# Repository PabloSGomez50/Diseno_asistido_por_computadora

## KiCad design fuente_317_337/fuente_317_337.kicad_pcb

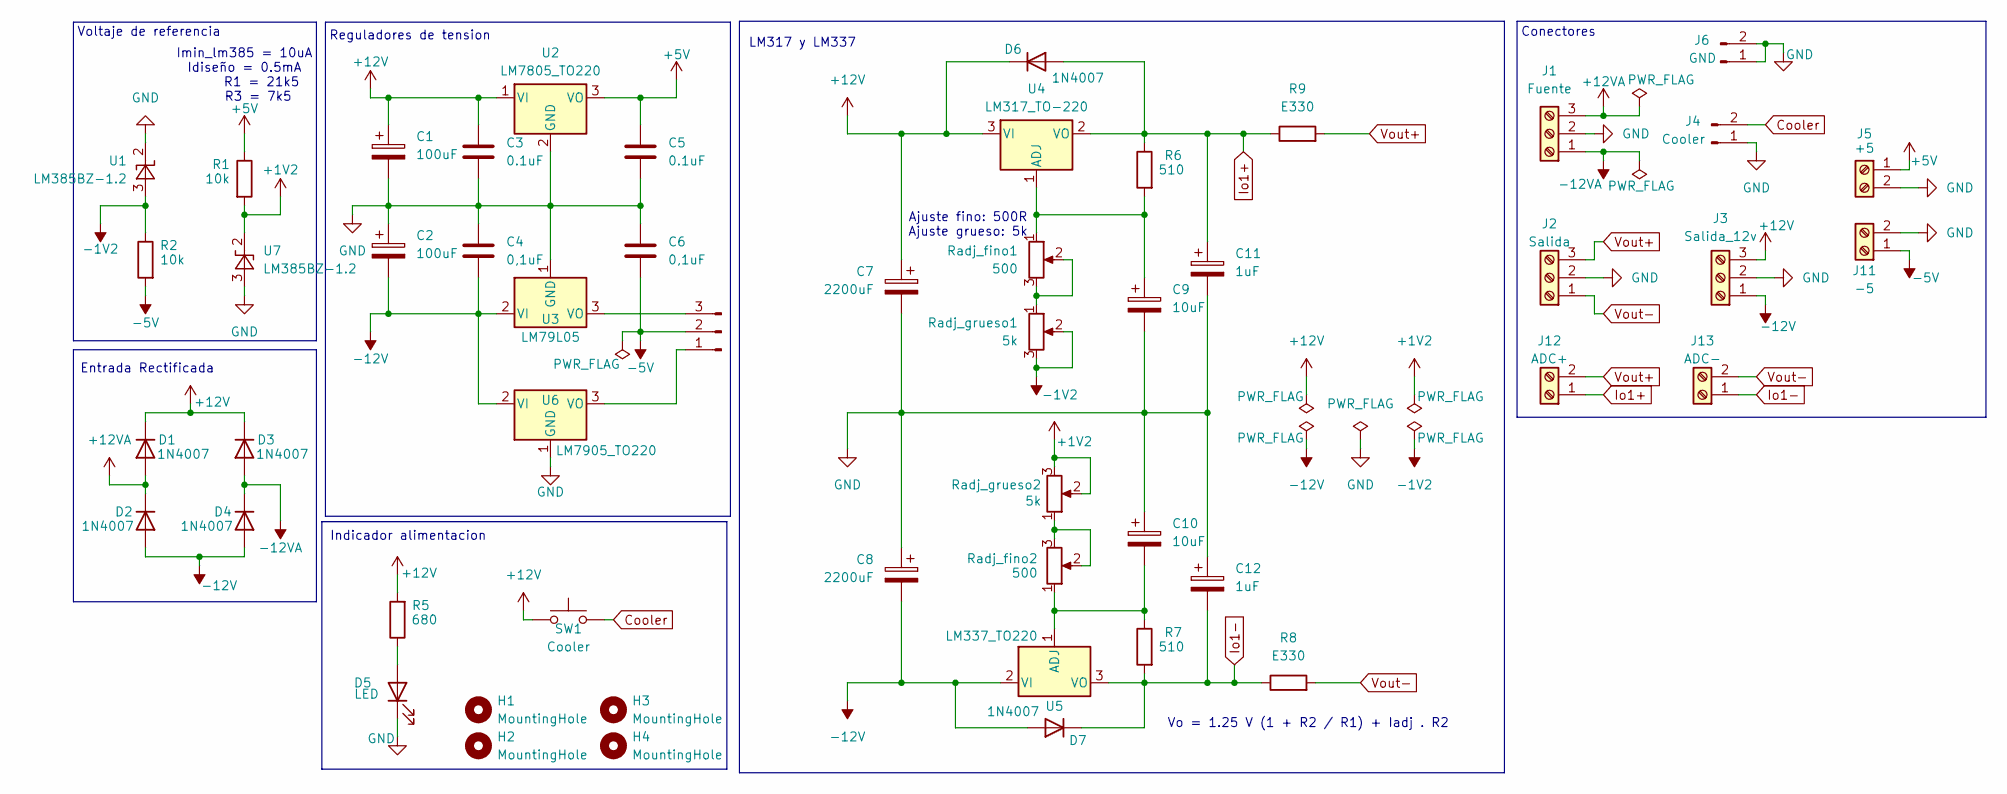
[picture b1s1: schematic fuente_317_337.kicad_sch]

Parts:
C1, C2: 100uF; CP_Radial_D5.0mm_P2.50mm
C3, C5: 0.1uF; C_Disc_D3.0mm_W2.0mm_P2.50mm
C4, C6: 0,1uF; C_Disc_D3.0mm_W2.0mm_P2.50mm
C7, C8: 2200uF; CP_Radial_D16.0mm_P7.50mm
C9, C10: 10uF; CP_Radial_D5.0mm_P2.50mm
C11, C12: 1uF; CP_Radial_D5.0mm_P2.50mm
D1, D2, D3, D4, D6, D7: 1N4007; D_DO-41_SOD81_P10.16mm_Horizontal
D5: LED; LED_D5.0mm
H1, H2, H3, H4: MountingHole; MountingHole_3.2mm_M3
J1: Fuente; TerminalBlock_Phoenix_MKDS-1,5-3-5.08_1x03_P5.08mm_Horizont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
J2: Salida; TerminalBlock_Phoenix_MKDS-1,5-3-5.08_1x03_P5.08mm_Horizont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
J3: Salida_12v; TerminalBlock_Phoenix_MKDS-1,5-3-5.08_1x03_P5.08mm_Horizont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
J4: Cooler; PinHeader_1x02_P2.54mm_Vertical
J5: +5; TerminalBlock_Phoenix_MKDS-1,5-2-5.08_1x02_P5.08mm_Horizont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
J6: GND; PinHeader_1x02_P2.54mm_Vertical
J10: SEL_7905; PinHeader_1x03_P2.54mm_Vertical
J11: -5; TerminalBlock_Phoenix_MKDS-1,5-2-5.08_1x02_P5.08mm_Horizont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
J12: ADC+; TerminalBlock_Phoenix_MKDS-1,5-2-5.08_1x02_P5.08mm_Horizont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
J13: ADC-; TerminalBlock_Phoenix_MKDS-1,5-2-5.08_1x02_P5.08mm_Horizont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
R1: 10k; R_Axial_DIN0207_L6.3mm_D2.5mm_P10.16mm_Horizontal
R2: 10k; R_Axial_DIN0207_L6.3mm_D2.5mm_P5.08mm_Vertical
R5: 680; R_Axial_DIN0207_L6.3mm_D2.5mm_P10.16mm_Horizontal
R6: 510; R_Axial_DIN0207_L6.3mm_D2.5mm_P2.54mm_Vertical
R7: 510; R_Axial_DIN0207_L6.3mm_D2.5mm_P10.16mm_Horizontal
R8, R9: E330; R_Axial_Power_L25.0mm_W6.4mm_P30.48mm
Radj_fino1, Radj_fino2: 500; PinHeader_1x03_P2.54mm_Vertical
Radj_grueso1, Radj_grueso2: 5k; PinHeader_1x03_P2.54mm_Vertical
SW1: Cooler; PinHeader_1x02_P2.54mm_Vertical
U1, U7: LM385BZ-1.2; TO-92_Inline
U2: LM7805_TO220; TO-220-3_Vertical
U3: LM79L05; TO-92_Inline
U4: LM317_TO-220; TO-220-3_Vertical
U5: LM337_TO220; TO-220-3_Vertical
U6: LM7905_TO220; TO-220-3_Vertical

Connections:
+1V2: R1.2, Radj_grueso2.2, Radj_grueso2.3, U7.2 (K)
+5V: C5.1, J5.1, R1.1, U2.3 (VO)
+12V: C1.1, C3.1, C7.1, D1.1 (K), D3.1 (K), D6.1 (K), J3.3, R5.2, SW1.1, U2.1 (VI), U4.3 (VI)
+12VA: D1.2 (A), D2.1 (K), J1.3
-1V2: R2.1, Radj_grueso1.2, Radj_grueso1.3, U1.3 (A)
-5V: C6.2, J10.2, J11.1, R2.2
-12V: C2.2, C4.2, C8.2, D2.2 (A), D4.2 (A), D7.2 (A), J3.1, U3.2 (VI), U5.2 (VI), U6.2 (VI)
-12VA: D3.2 (A), D4.1 (K), J1.1
Cooler: J4.2, SW1.2
GND: C1.2, C2.1, C3.2, C4.1, C5.2, C6.1, C7.2, C8.1, C9.2, C10.1, C11.2, C12.1, D5.1 (K), J1.2, J2.2, J3.2, J4.1, J5.2, J6.1, J6.2, J11.2, U1.2 (K), U2.2 (GND), U3.1 (GND), U6.1 (GND), U7.3 (A)
Io1+: C11.1, D6.2 (A), J12.1, R6.1, R9.1, U4.2 (VO)
Io1-: C12.2, D7.1 (K), J13.1, R7.2, R8.1, U5.3 (VO)
unnamed: D5.2 (A), R5.1
unnamed: J10.1, U6.3 (VO)
unnamed: J10.3, U3.3 (VO)
unnamed: Radj_fino1.2, Radj_fino1.3, Radj_grueso1.1
unnamed: Radj_fino2.2, Radj_fino2.3, Radj_grueso2.1
unnamed: C9.1, R6.2, Radj_fino1.1, U4.1 (ADJ)
unnamed: C10.2, R7.1, Radj_fino2.1, U5.1 (ADJ)
Vout+: J2.3, J12.2, R9.2
Vout-: J2.1, J13.2, R8.2

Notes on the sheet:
Indicador alimentacion
Vo = 1.25 V (1 + R2 / R1) + Iadj . R2
LM317 y LM337
Voltaje de referencia
Imin_lm385 = 10uA Idiseño = 0.5mA R1 = 21k5 R3 = 7k5
Reguladores de tension
Entrada Rectificada
Ajuste fino: 500R Ajuste grueso: 5k
Conectores

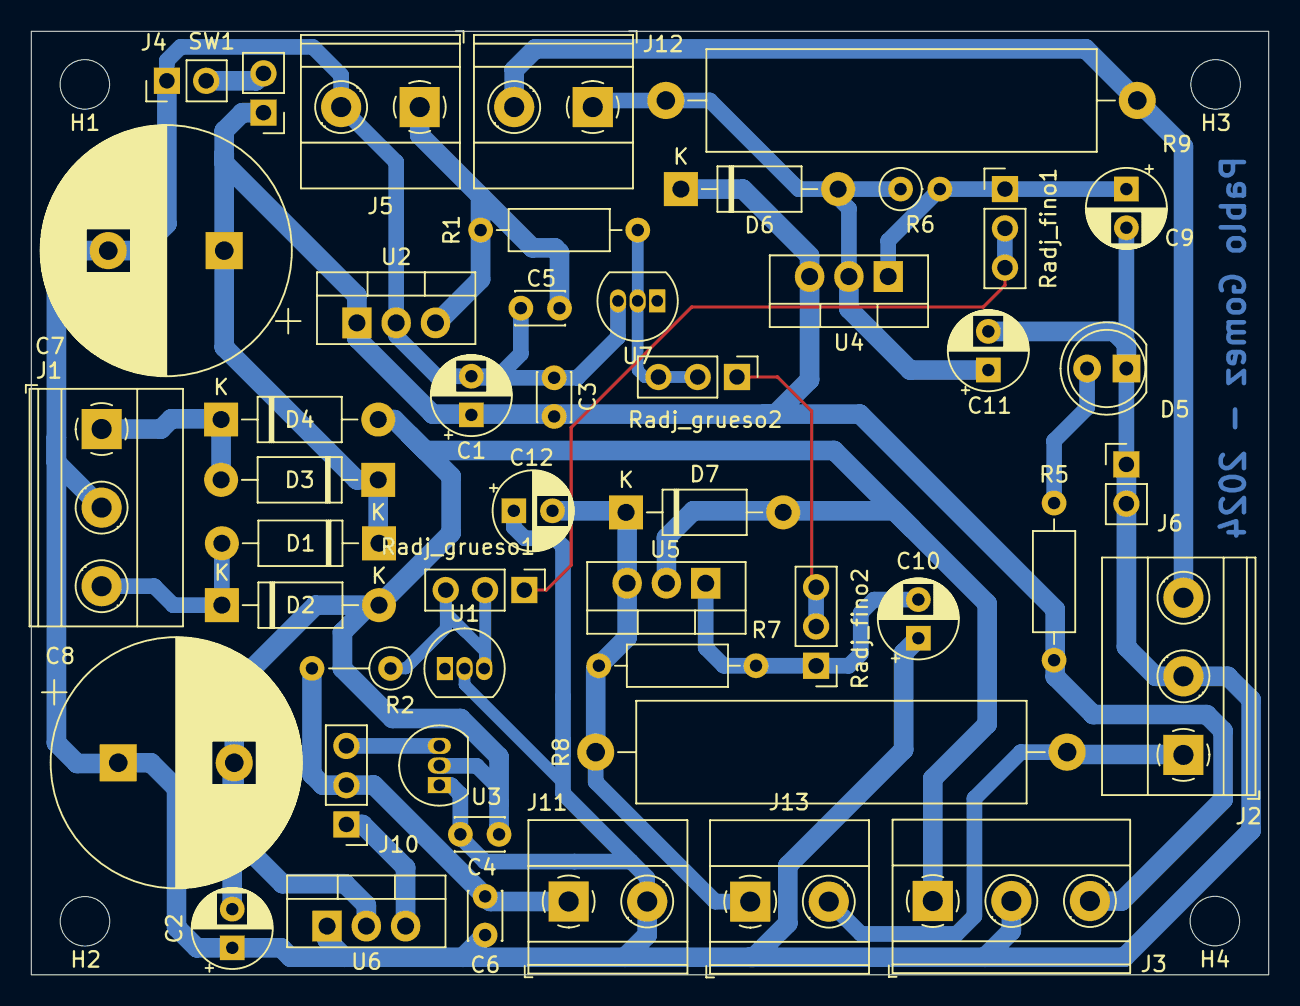
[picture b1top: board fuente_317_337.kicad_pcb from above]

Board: 2 copper layers, 80.0 x 61.0 mm, 52 parts (0 on the bottom side), 21 nets.

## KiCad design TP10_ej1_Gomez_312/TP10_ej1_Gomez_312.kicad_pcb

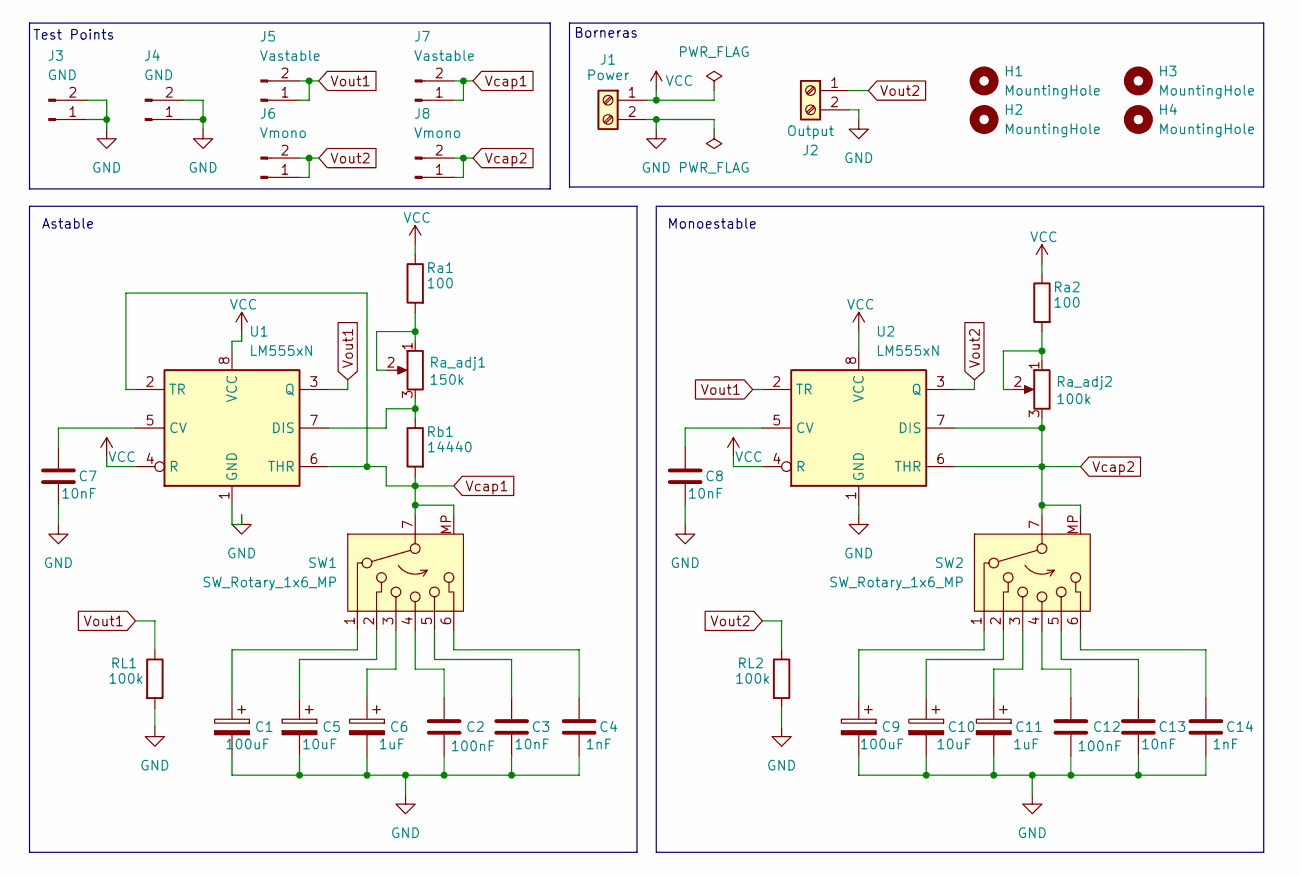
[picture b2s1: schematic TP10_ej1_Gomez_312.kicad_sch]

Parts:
C1, C9: 100uF; CP_Radial_D5.0mm_P2.50mm
C2, C12: 100nF; C_Disc_D3.0mm_W2.0mm_P2.50mm
C3, C7, C8, C13: 10nF; C_Disc_D3.0mm_W2.0mm_P2.50mm
C4, C14: 1nF; C_Disc_D3.0mm_W2.0mm_P2.50mm
C5, C10: 10uF; CP_Radial_D5.0mm_P2.50mm
C6, C11: 1uF; CP_Radial_D5.0mm_P2.50mm
H1, H2, H3, H4: MountingHole; MountingHole_3.2mm_M3
J1: Power; TerminalBlock_Phoenix_MKDS-1,5-2-5.08_1x02_P5.08mm_Horizont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
J2: Output; BNC_TEConnectivity_1478035_Horizontal
J3, J4: GND; PinHeader_1x02_P2.54mm_Vertical
J5, J7: Vastable; PinHeader_1x02_P2.54mm_Vertical
J6, J8: Vmono; PinHeader_1x02_P2.54mm_Vertical
RL1, RL2: 100k; R_Axial_DIN0207_L6.3mm_D2.5mm_P10.16mm_Horizontal
Ra1, Ra2: 100; R_Axial_DIN0207_L6.3mm_D2.5mm_P10.16mm_Horizontal
Ra_adj1: 150k; PinHeader_1x03_P2.54mm_Vertical
Ra_adj2: 100k; PinHeader_1x03_P2.54mm_Vertical
Rb1: 14440; R_Axial_DIN0207_L6.3mm_D2.5mm_P10.16mm_Horizontal
SW1, SW2: SW_Rotary_1x6_MP; SW_NKK_NR01
U1, U2: LM555xN; DIP-8_W7.62mm

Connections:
GND: C1.2, C2.2, C3.2, C4.2, C5.2, C6.2, C7.2, C8.2, C9.2, C10.2, C11.2, C12.2, C13.2, C14.2, J1.2, J2.2, J3.1, J3.2, J4.1, J4.2, RL1.2, RL2.2, U1.1 (GND), U2.1 (GND)
unnamed: C1.1, SW1.1
unnamed: C2.1, SW1.4
unnamed: C3.1, SW1.5
unnamed: C4.1, SW1.6
unnamed: C5.1, SW1.2
unnamed: C6.1, SW1.3
unnamed: C9.1, SW2.1
unnamed: C10.1, SW2.2
unnamed: C11.1, SW2.3
unnamed: C12.1, SW2.4
unnamed: C13.1, SW2.5
unnamed: C14.1, SW2.6
unnamed: Ra1.2, Ra_adj1.1, Ra_adj1.2
unnamed: Ra2.2, Ra_adj2.1, Ra_adj2.2
unnamed: C7.1, U1.5 (CV)
unnamed: Ra_adj1.3, Rb1.1, U1.7 (DIS)
unnamed: C8.1, U2.5 (CV)
VCC: J1.1, Ra1.1, Ra2.1, U1.4 (R), U1.8 (VCC), U2.4 (R), U2.8 (VCC)
Vcap1: J7.1, J7.2, Rb1.2, SW1.7, SW1.MP, U1.2 (TR), U1.6 (THR)
Vcap2: J8.1, J8.2, Ra_adj2.3, SW2.7, SW2.MP, U2.6 (THR), U2.7 (DIS)
Vout1: J5.1, J5.2, RL1.1, U1.3 (Q), U2.2 (TR)
Vout2: J2.1, J6.1, J6.2, RL2.1, U2.3 (Q)

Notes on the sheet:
Astable
Test Points
Monoestable
Borneras

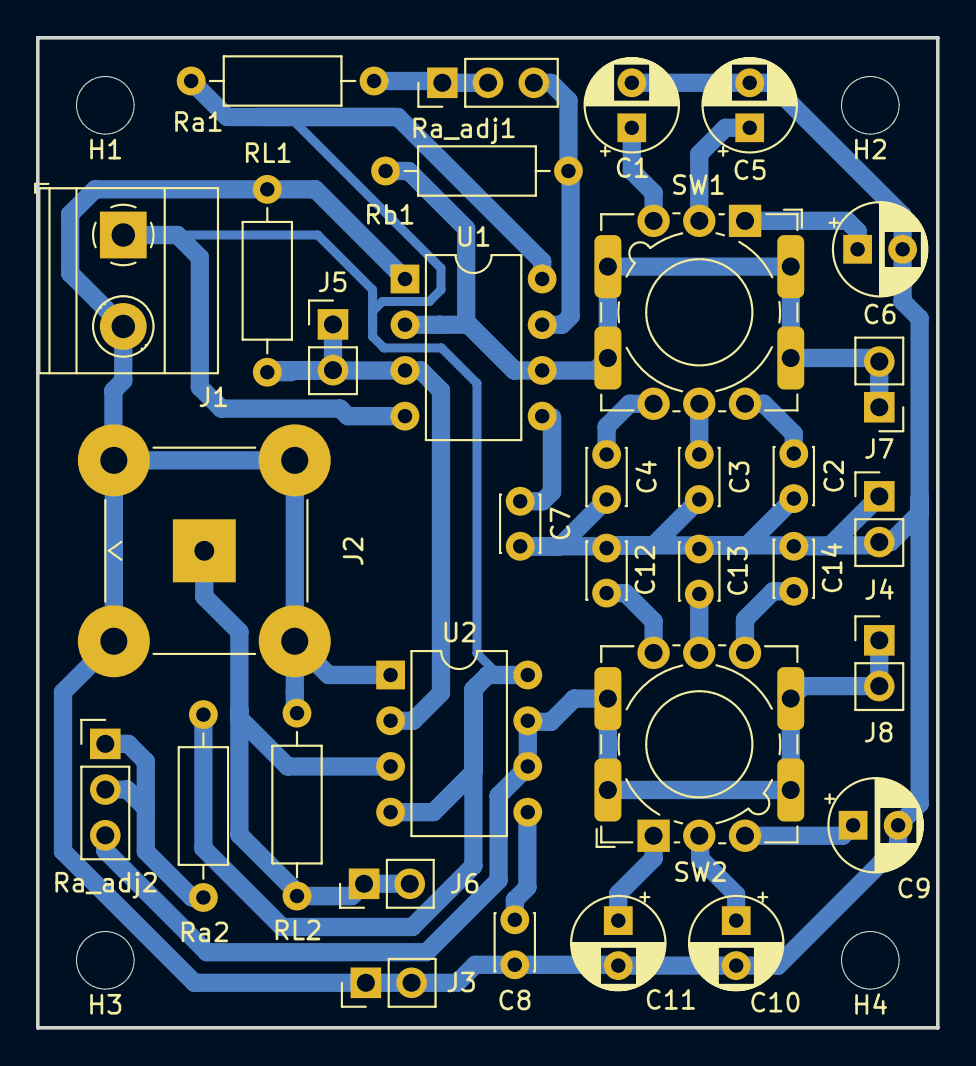
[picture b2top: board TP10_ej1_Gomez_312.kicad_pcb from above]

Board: 2 copper layers, 50.0 x 55.0 mm, 37 parts (0 on the bottom side), 23 nets.

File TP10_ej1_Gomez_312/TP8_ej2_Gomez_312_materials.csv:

"Reference","Value","Datasheet","Footprint","Qty","DNP"
"C1,C9","100uF","~","Capacitor_THT:CP_Radial_D5.0mm_P2.50mm","2",""
"C2,C12","100nF","~","Capacitor_THT:C_Disc_D3.0mm_W2.0mm_P2.50mm","2",""
"C3,C7,C8,C13","10nF","~","Capacitor_THT:C_Disc_D3.0mm_W2.0mm_P2.50mm","4",""
"C4,C14","1nF","~","Capacitor_THT:C_Disc_D3.0mm_W2.0mm_P2.50mm","2",""
"C5,C10","10uF","~","Capacitor_THT:CP_Radial_D5.0mm_P2.50mm","2",""
"C6,C11","1uF","~","Capacitor_THT:CP_Radial_D5.0mm_P2.50mm","2",""
"J1","Power","~","TerminalBlock_Phoenix:TerminalBlock_Phoenix_MKDS-1,5-2-5.08_1x02_P5.08mm_Horizontal","1",""
"J2","Output","~","Connector_Coaxial:BNC_TEConnectivity_1478035_Horizontal","1",""
"J3,J4","GND","~","Connector_PinHeader_2.54mm:PinHeader_1x02_P2.54mm_Vertical","2",""
"J5,J7","Vastable","~","Connector_PinHeader_2.54mm:PinHeader_1x02_P2.54mm_Vertical","2",""
"J6,J8","Vmono","~","Connector_PinHeader_2.54mm:PinHeader_1x02_P2.54mm_Vertical","2",""
"Ra1,Ra2","100","~","Resistor_THT:R_Axial_DIN0207_L6.3mm_D2.5mm_P10.16mm_Horizontal","2",""
"Ra_adj1","150k","~","Connector_PinHeader_2.54mm:PinHeader_1x03_P2.54mm_Vertical","1",""
"Ra_adj2,RL1,RL2","100k","~","-- mixed values --","3",""
"Rb1","14440","~","Resistor_THT:R_Axial_DIN0207_L6.3mm_D2.5mm_P10.16mm_Horizontal","1",""
"SW1,SW2","SW_Rotary_1x6_MP","~","Button_Switch_THT:SW_NKK_NR01","2",""
"U1,U2","LM555xN","http://www.ti.com/lit/ds/symlink/lm555.pdf","Package_DIP:DIP-8_W7.62mm","2",""

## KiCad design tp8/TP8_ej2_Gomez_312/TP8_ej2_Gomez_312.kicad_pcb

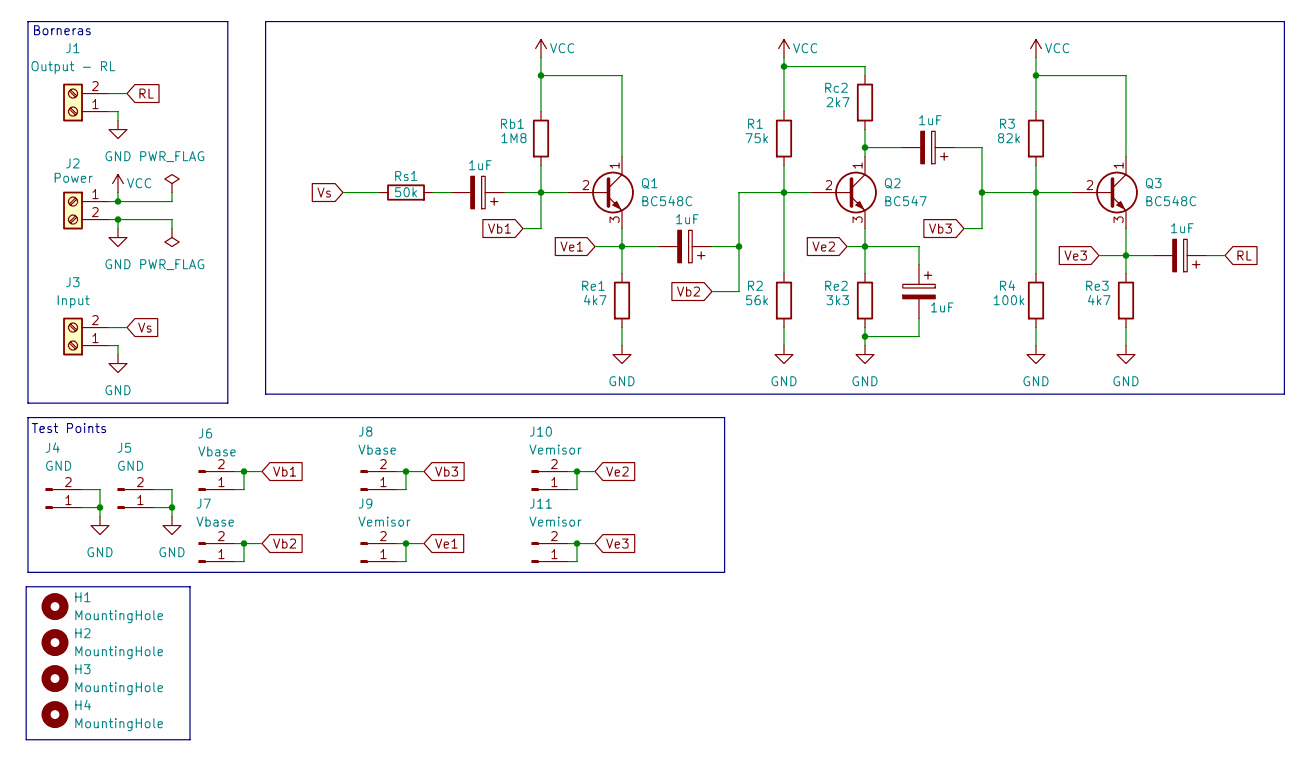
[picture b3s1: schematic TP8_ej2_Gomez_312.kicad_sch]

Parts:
C1, C2, C3, C4, C5: 1uF; CP_Radial_D5.0mm_P2.50mm
H1, H2, H3, H4: MountingHole; MountingHole_3.2mm_M3
J1: Output - RL; TerminalBlock_Phoenix_MKDS-1,5-2-5.08_1x02_P5.08mm_Horizont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
J2: Power; TerminalBlock_Phoenix_MKDS-1,5-2-5.08_1x02_P5.08mm_Horizont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
J3: Input; TerminalBlock_Phoenix_MKDS-1,5-2-5.08_1x02_P5.08mm_Horizont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
J4, J5: GND; PinHeader_1x02_P2.54mm_Vertical
J6, J7, J8: Vbase; PinHeader_1x02_P2.54mm_Vertical
J9, J10, J11: Vemisor; PinHeader_1x02_P2.54mm_Vertical
Q1, Q3: BC548C; TO-92_Inline
Q2: BC547; TO-92_Inline
R1: 75k; R_Axial_DIN0207_L6.3mm_D2.5mm_P10.16mm_Horizontal
R2: 56k; R_Axial_DIN0207_L6.3mm_D2.5mm_P10.16mm_Horizontal
R3: 82k; R_Axial_DIN0207_L6.3mm_D2.5mm_P10.16mm_Horizontal
R4: 100k; R_Axial_DIN0207_L6.3mm_D2.5mm_P10.16mm_Horizontal
Rb1: 1M8; R_Axial_DIN0207_L6.3mm_D2.5mm_P10.16mm_Horizontal
Rc2: 2k7; R_Axial_DIN0207_L6.3mm_D2.5mm_P10.16mm_Horizontal
Re1, Re3: 4k7; R_Axial_DIN0207_L6.3mm_D2.5mm_P10.16mm_Horizontal
Re2: 3k3; R_Axial_DIN0207_L6.3mm_D2.5mm_P10.16mm_Horizontal
Rs1: 50k; R_Axial_DIN0207_L6.3mm_D2.5mm_P10.16mm_Horizontal

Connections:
GND: C5.2, J1.1, J2.2, J3.1, J4.1, J4.2, J5.1, J5.2, R2.2, R4.2, Re1.2, Re2.2, Re3.2
unnamed: C1.2, Rs1.2
unnamed: C3.2, Q2.1 (C), Rc2.2
RL: C4.1, J1.2
VCC: J2.1, Q1.1 (C), Q3.1 (C), R1.1, R3.1, Rb1.1, Rc2.1
Vb1: C1.1, J6.1, J6.2, Q1.2 (B), Rb1.2
Vb2: C2.1, J7.1, J7.2, Q2.2 (B), R1.2, R2.1
Vb3: C3.1, J8.1, J8.2, Q3.2 (B), R3.2, R4.1
Ve1: C2.2, J9.1, J9.2, Q1.3 (E), Re1.1
Ve2: C5.1, J10.1, J10.2, Q2.3 (E), Re2.1
Ve3: C4.2, J11.1, J11.2, Q3.3 (E), Re3.1
Vs: J3.2, Rs1.1

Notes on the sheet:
Test Points
Borneras

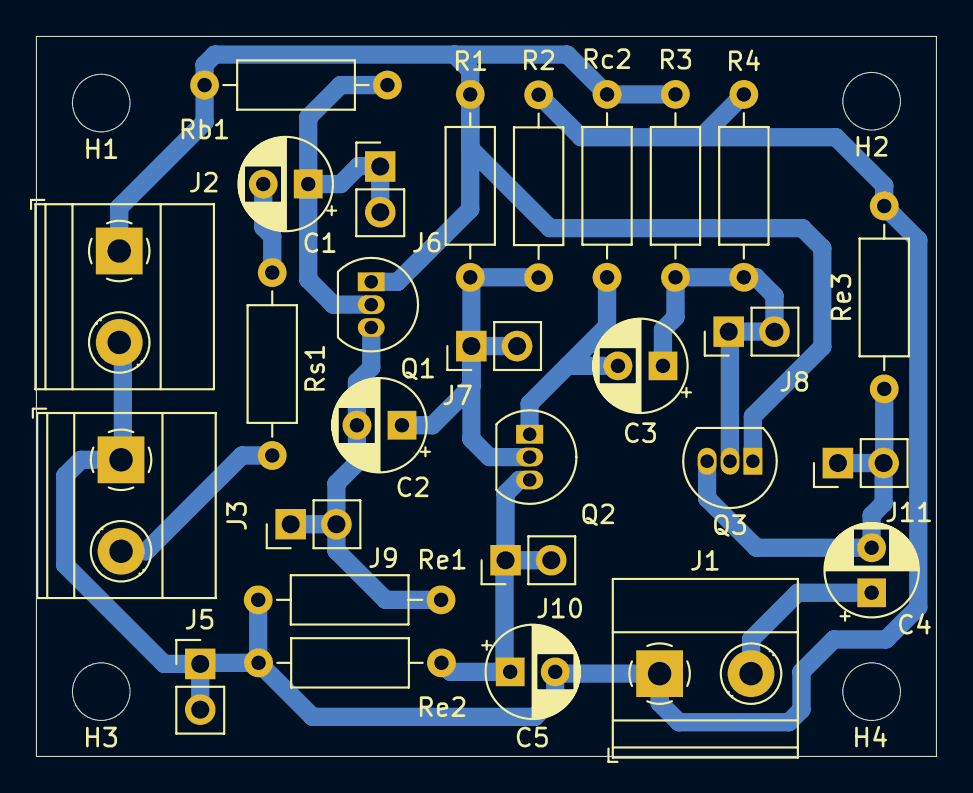
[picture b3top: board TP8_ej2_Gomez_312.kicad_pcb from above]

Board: 2 copper layers, 50.0 x 40.0 mm, 32 parts (0 on the bottom side), 12 nets.

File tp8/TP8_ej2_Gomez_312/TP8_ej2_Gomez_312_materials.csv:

"Reference","Value","Datasheet","Footprint","Qty","DNP"
"C1,C2,C3,C4,C5","1uF","~","Capacitor_THT:CP_Radial_D5.0mm_P2.50mm","5",""
"J1","Output - RL","~","TerminalBlock_Phoenix:TerminalBlock_Phoenix_MKDS-1,5-2-5.08_1x02_P5.08mm_Horizontal","1",""
"J2","Power","~","TerminalBlock_Phoenix:TerminalBlock_Phoenix_MKDS-1,5-2-5.08_1x02_P5.08mm_Horizontal","1",""
"J3","Input","~","TerminalBlock_Phoenix:TerminalBlock_Phoenix_MKDS-1,5-2-5.08_1x02_P5.08mm_Horizontal","1",""
"J4,J5","GND","~","Connector_PinHeader_2.54mm:PinHeader_1x02_P2.54mm_Vertical","2",""
"J6,J7,J8","Vbase","~","Connector_PinHeader_2.54mm:PinHeader_1x02_P2.54mm_Vertical","3",""
"J9,J10,J11","Vemisor","~","Connector_PinHeader_2.54mm:PinHeader_1x02_P2.54mm_Vertical","3",""
"Q1,Q3","BC548C","https://www.onsemi.com/pub/Collateral/BC550-D.pdf","Package_TO_SOT_THT:TO-92_Inline","2",""
"Q2","BC547","https://www.onsemi.com/pub/Collateral/BC550-D.pdf","Package_TO_SOT_THT:TO-92_Inline","1",""
"R1","75k","~","Resistor_THT:R_Axial_DIN0207_L6.3mm_D2.5mm_P10.16mm_Horizontal","1",""
"R2","56k","~","Resistor_THT:R_Axial_DIN0207_L6.3mm_D2.5mm_P10.16mm_Horizontal","1",""
"R3","82k","~","Resistor_THT:R_Axial_DIN0207_L6.3mm_D2.5mm_P10.16mm_Horizontal","1",""
"R4","100k","~","Resistor_THT:R_Axial_DIN0207_L6.3mm_D2.5mm_P10.16mm_Horizontal","1",""
"Rb1","1M8","~","Resistor_THT:R_Axial_DIN0207_L6.3mm_D2.5mm_P10.16mm_Horizontal","1",""
"Rc2","2k7","~","Resistor_THT:R_Axial_DIN0207_L6.3mm_D2.5mm_P10.16mm_Horizontal","1",""
"Re1,Re3","4k7","~","Resistor_THT:R_Axial_DIN0207_L6.3mm_D2.5mm_P10.16mm_Horizontal","2",""
"Re2","3k3","~","Resistor_THT:R_Axial_DIN0207_L6.3mm_D2.5mm_P10.16mm_Horizontal","1",""
"Rs1","50k","~","Resistor_THT:R_Axial_DIN0207_L6.3mm_D2.5mm_P10.16mm_Horizontal","1",""

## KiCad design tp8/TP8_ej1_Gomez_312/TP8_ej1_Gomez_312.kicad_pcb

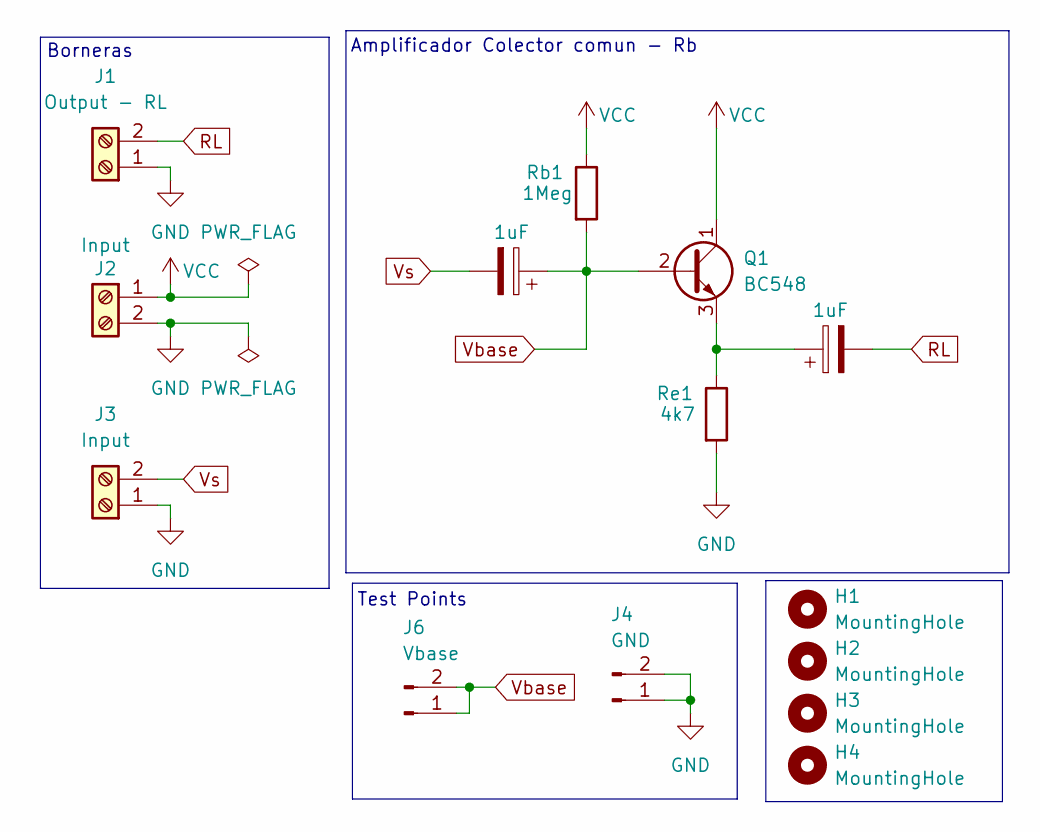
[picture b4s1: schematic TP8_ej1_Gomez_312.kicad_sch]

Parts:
C1, C2: 1uF; CP_Radial_D5.0mm_P2.50mm
H1, H2, H3, H4: MountingHole; MountingHole_3.2mm_M3
J1: Output - RL; TerminalBlock_bornier-2_P5.08mm
J2, J3: Input; TerminalBlock_bornier-2_P5.08mm
J4: GND; PinHeader_1x02_P2.54mm_Vertical
J6: Vbase; PinHeader_1x02_P2.54mm_Vertical
Q1: BC548; TO-92_Inline
Rb1: 1Meg; R_Axial_DIN0207_L6.3mm_D2.5mm_P10.16mm_Horizontal
Re1: 4k7; R_Axial_DIN0207_L6.3mm_D2.5mm_P10.16mm_Horizontal

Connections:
GND: J1.1, J2.2, J3.1, J4.1, J4.2, Re1.2
unnamed: C2.1, Q1.3 (E), Re1.1
RL: C2.2, J1.2
VCC: J2.1, Q1.1 (C), Rb1.1
Vbase: C1.1, J6.1, J6.2, Q1.2 (B), Rb1.2
Vs: C1.2, J3.2

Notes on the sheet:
Test Points
Amplificador Colector comun - Rb
Borneras

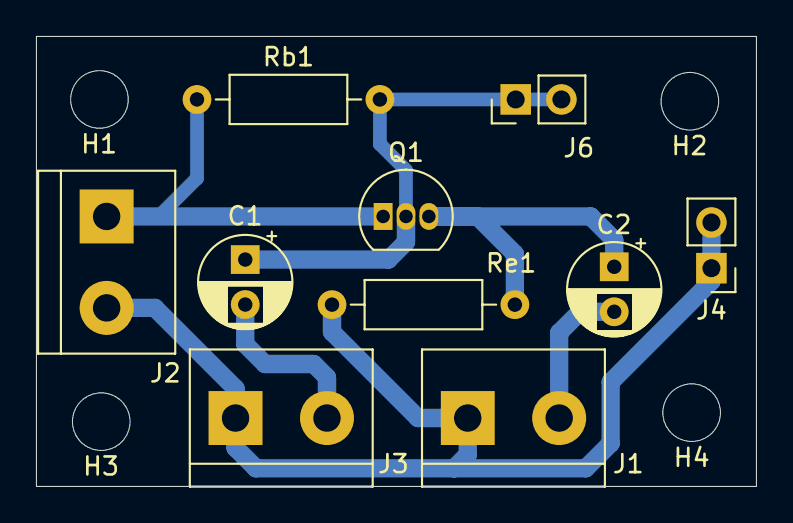
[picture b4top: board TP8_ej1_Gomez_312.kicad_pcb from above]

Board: 2 copper layers, 40.0 x 25.0 mm, 14 parts (0 on the bottom side), 6 nets.

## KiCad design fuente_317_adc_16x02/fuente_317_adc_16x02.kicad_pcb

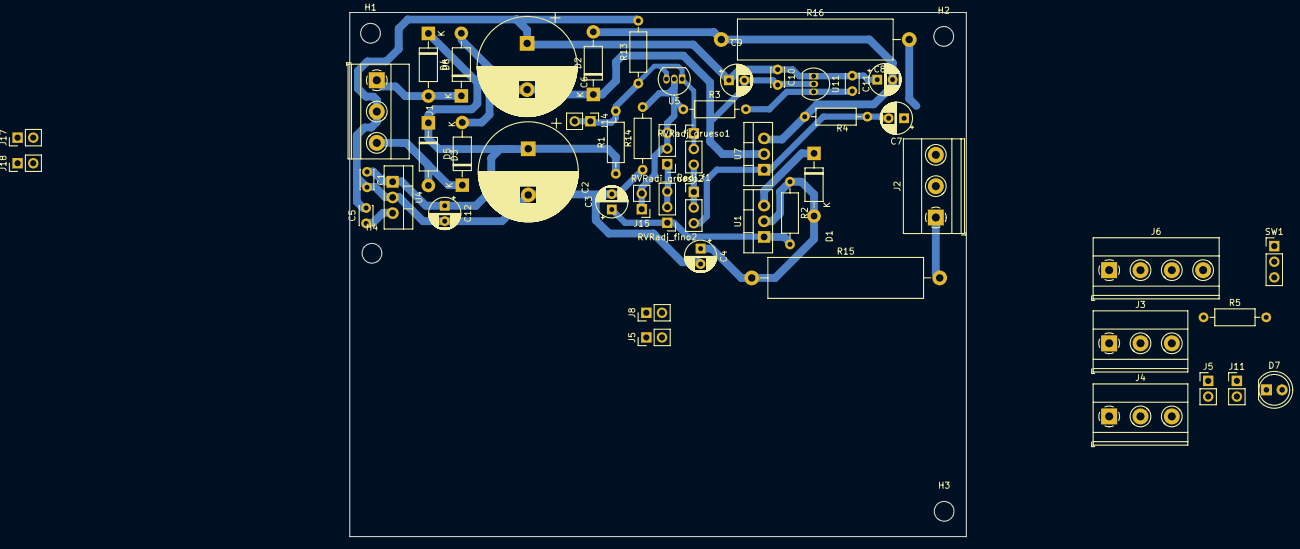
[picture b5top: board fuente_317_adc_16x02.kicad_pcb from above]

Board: 2 copper layers, 100.0 x 85.0 mm, 55 parts (0 on the bottom side), 23 nets.

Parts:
C1, C5: 0.1uF; C_Disc_D3.0mm_W2.0mm_P2.50mm
C2, C6: 2200uF; CP_Radial_D16.0mm_P7.50mm
C3, C7: 10uF; CP_Radial_D5.0mm_P2.50mm
C4, C8: 1uF; CP_Radial_D5.0mm_P2.50mm
C9, C12: 100uF; CP_Radial_D5.0mm_P2.50mm
C10, C11: 0,1uF; C_Disc_D3.0mm_W2.0mm_P2.50mm
D1, D2, D3, D4, D5, D6: 1N4007; D_DO-41_SOD81_P10.16mm_Horizontal
D7: LED; LED_D5.0mm
H1, H2, H3, H4: MountingHole; MountingHole_3.2mm_M3
J1: Fuente; TerminalBlock_Phoenix_MKDS-1,5-3-5.08_1x03_P5.08mm_Horizont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
J2: Salida; TerminalBlock_Phoenix_MKDS-1,5-3-5.08_1x03_P5.08mm_Horizont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
J3: Salida_5v; TerminalBlock_Phoenix_MKDS-1,5-3-5.08_1x03_P5.08mm_Horizont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
J4: Salida_12v; TerminalBlock_Phoenix_MKDS-1,5-3-5.08_1x03_P5.08mm_Horizont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
J5, J17: Vadj+; PinHeader_1x02_P2.54mm_Vertical
J5#2: Cooler; PinHeader_1x02_P2.54mm_Vertical
J6: Inputs; TerminalBlock_Phoenix_MKDS-1,5-4-5.08_1x04_P5.08mm_Horizont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
J8, J18: Vadj-; PinHeader_1x02_P2.54mm_Vertical
J11: GND; PinHeader_1x02_P2.54mm_Vertical
J14: +1.2V; PinHeader_1x02_P2.54mm_Vertical
J15: -1.2V; PinHeader_1x02_P2.54mm_Vertical
R1, R3: 22k; R_Axial_DIN0207_L6.3mm_D2.5mm_P10.16mm_Horizontal
R2, R4: 510; R_Axial_DIN0207_L6.3mm_D2.5mm_P10.16mm_Horizontal
R5: 200; R_Axial_DIN0207_L6.3mm_D2.5mm_P10.16mm_Horizontal
R13, R14: 10k; R_Axial_DIN0207_L6.3mm_D2.5mm_P10.16mm_Horizontal
R15, R16: E330; R_Axial_Power_L25.0mm_W6.4mm_P30.48mm
RVRadj_fino2: 500; PinHeader_1x03_P2.54mm_Vertical
RVRadj_grueso1, RVRadj_grueso2: 5k; PinHeader_1x03_P2.54mm_Vertical
Radj_f1: 500; PinHeader_1x03_P2.54mm_Vertical
SW1: SW_SPDT; PinHeader_1x03_P2.54mm_Vertical
U1: LM317_TO-220; TO-220-3_Vertical
U4: LM7805_TO220; TO-220-3_Vertical
U5: LM385; TO-92_Inline
U7: LM337_TO220; TO-220-3_Vertical
U11: LM79L05; TO-92_Inline

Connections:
+1V2: J14.1, J14.2, R1.2, R13.1, RVRadj_grueso1.1, RVRadj_grueso1.2, U5.1 (REF), U5.3 (K)
+5V: C5.1, J3.1, R1.1, R5.1, U4.3 (VO)
+12V: C1.1, C2.1, C12.1, D1.1 (K), D3.1 (K), D4.1 (K), J4.1, SW1.2 (B), U1.3 (VI), U4.1 (VI)
+12VA: D3.2 (A), D5.1 (K), J1.3
-1V2: J15.1, J15.2, R3.1, R14.2, RVRadj_grueso2.2, RVRadj_grueso2.3, U5.2 (A)
-5V: C11.2, J3.3, R3.2, U11.3 (VO)
-12V: C6.2, C9.2, C10.2, D2.1 (K), D5.2 (A), D6.2 (A), J4.3, U7.2 (VI), U11.2 (VI)
-12VA: D4.2 (A), D6.1 (K), J1.1
Cooler: J5#2.2, SW1.3 (C)
GND: C1.2, C2.2, C3.2, C4.2, C5.2, C6.1, C7.1, C8.1, C9.1, C10.1, C11.1, C12.2, D7.1 (K), J1.2, J2.2, J3.2, J4.2, J5#2.1, J11.1, J11.2, R13.2, R14.1, U4.2 (GND), U11.1 (GND)
Iadc+: J18.1, J18.2
Iadc-: J8.1, J8.2
Io1+: C4.1, D1.2 (A), J6.2, R2.1, R15.1, U1.2 (VO)
Io1-: C8.2, D2.2 (A), J6.4, R4.2, R16.1, U7.3 (VO)
unnamed: D7.2 (A), R5.2
unnamed: RVRadj_fino2.2, RVRadj_fino2.3, RVRadj_grueso2.1
unnamed: RVRadj_grueso1.3, Radj_f1.1, Radj_f1.2
unnamed: C3.1, R2.2, RVRadj_fino2.1, U1.1 (ADJ)
unnamed: C7.2, R4.1, Radj_f1.3, U7.1 (ADJ)
Vadc+: J17.1, J17.2
Vadc-: J5.1, J5.2
Vout+: J2.1, J6.1, R15.2
Vout-: J2.3, J6.3, R16.2

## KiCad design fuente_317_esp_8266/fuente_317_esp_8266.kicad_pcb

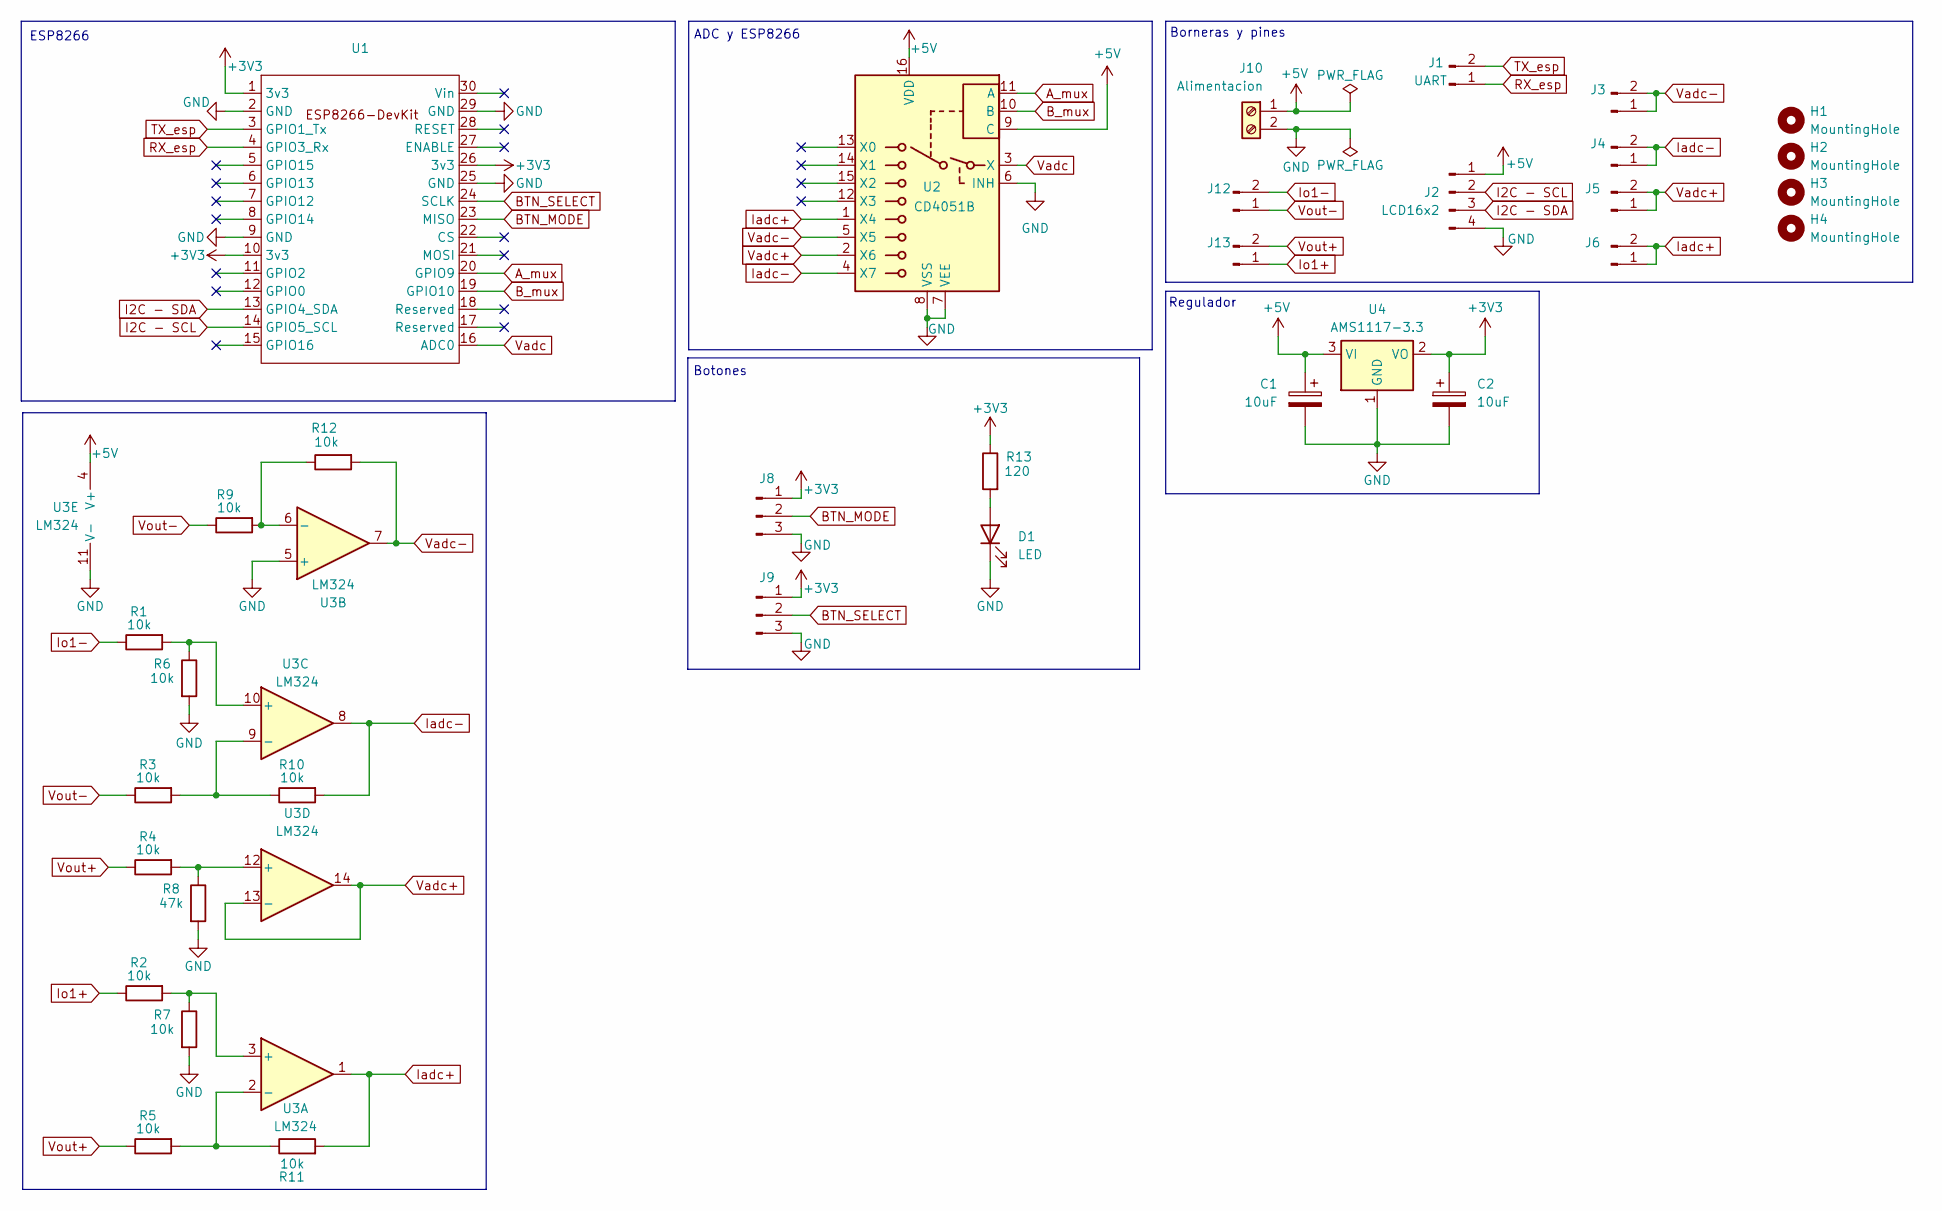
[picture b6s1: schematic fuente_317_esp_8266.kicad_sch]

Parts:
C1, C2: 10uF; CP_Radial_D5.0mm_P2.50mm
D1: LED; LED_D5.0mm
H1, H2, H3, H4: MountingHole; MountingHole_3.2mm_M3
J1: UART; PinHeader_1x02_P2.54mm_Vertical
J2: LCD16x2; PinHeader_1x04_P2.54mm_Vertical
J3, J5, J12: Vadj+; PinHeader_1x02_P2.54mm_Vertical
J4, J6, J13: Vadj-; PinHeader_1x02_P2.54mm_Vertical
J8: BTN_MODE; PinHeader_1x03_P2.54mm_Vertical
J9: BTN_SEL; PinHeader_1x03_P2.54mm_Vertical
J10: Alimentacion; TerminalBlock_Phoenix_MKDS-1,5-2-5.08_1x02_P5.08mm_Horizont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
R1, R2, R3, R4, R9, R12: 10k; R_Axial_DIN0207_L6.3mm_D2.5mm_P10.16mm_Horizontal
R5, R6, R7, R10, R11: 10k; R_Axial_DIN0207_L6.3mm_D2.5mm_P5.08mm_Vertical
R8: 47k; R_Axial_DIN0207_L6.3mm_D2.5mm_P5.08mm_Vertical
R13: 120; R_Axial_DIN0207_L6.3mm_D2.5mm_P10.16mm_Horizontal
U1: Esp-8266-DevKit
U2: CD4051B; CERDIP-16_W7.62mm_SideBrazed_Socket
U3: LM324; CERDIP-14_W7.62mm_SideBrazed_Socket
U4: AMS1117-3.3; SOT-223-3_TabPin2

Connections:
+3V3: C2.1, J8.1, J9.1, R13.1, U1.1 (3v3), U1.10 (3v3), U1.26 (3v3), U4.2 (VO)
+5V: C1.1, J2.1, J10.1, U2.9 (C), U2.16 (VDD), U3.4 (V+), U4.3 (VI)
A_mux: U1.20 (GPIO9), U2.11 (A)
BTN_MODE: J8.2, U1.23 (MISO)
BTN_SELECT: J9.2, U1.24 (SCLK)
B_mux: U1.19 (GPIO10), U2.10 (B)
GND: C1.2, C2.2, D1.1 (K), J2.4, J8.3, J9.3, J10.2, R6.2, R7.2, R8.2, U1.2 (GND), U1.9 (GND), U1.25 (GND), U1.29 (GND), U2.6 (INH), U2.7 (VEE), U2.8 (VSS), U3.5 (+), U3.11 (V-), U4.1 (GND)
I2C - SCL: J2.2, U1.14 (GPIO5_SCL)
I2C - SDA: J2.3, U1.13 (GPIO4_SDA)
Iadc+: J6.1, J6.2, R11.2, U2.1 (X4), U3.1
Iadc-: J4.1, J4.2, R10.2, U2.4 (X7), U3.8
Io1+: J13.1, R2.1
Io1-: J12.2, R1.1
unnamed: D1.2 (A), R13.2
unnamed: R2.2, R7.1, U3.3 (+)
unnamed: R5.2, R11.1, U3.2 (-)
unnamed: R9.2, R12.1, U3.6 (-)
unnamed: R1.2, R6.1, U3.10 (+)
unnamed: R3.2, R10.1, U3.9 (-)
unnamed: R4.2, R8.1, U3.12 (+)
RX_esp: J1.1, U1.4 (GPIO3_Rx)
TX_esp: J1.2, U1.3 (GPIO1_Tx)
Vadc: U1.16 (ADC0), U2.3 (X)
Vadc+: J5.1, J5.2, U2.2 (X6), U3.13 (-), U3.14
Vadc-: J3.1, J3.2, R12.2, U2.5 (X5), U3.7
Vout+: J13.2, R4.1, R5.1
Vout-: J12.1, R3.1, R9.1

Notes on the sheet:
ADC y ESP8266
Botones
Regulador
Borneras y pines
ESP8266

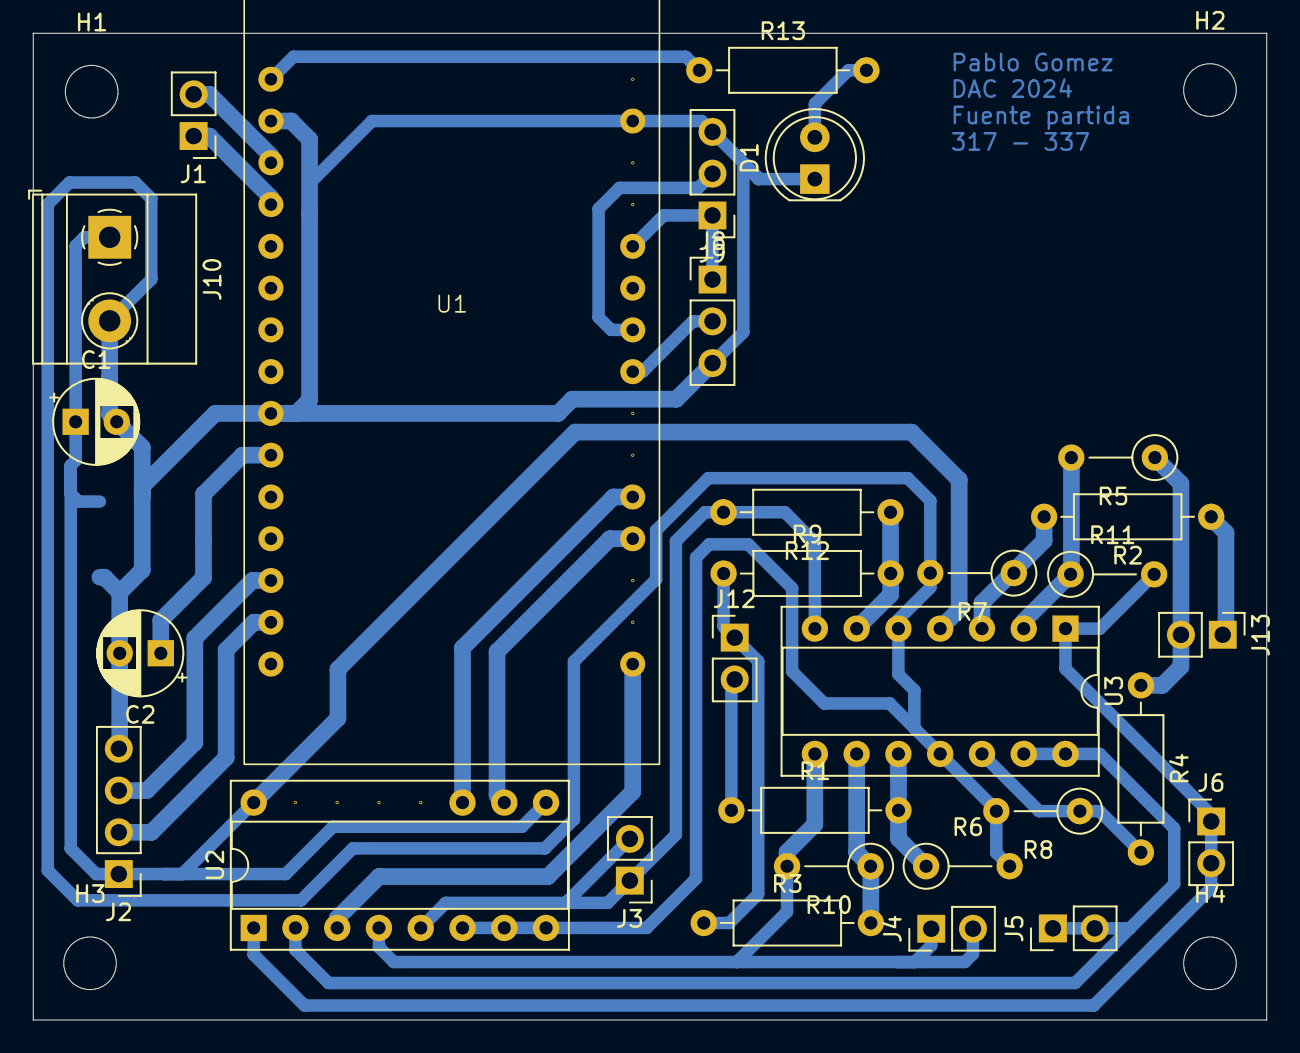
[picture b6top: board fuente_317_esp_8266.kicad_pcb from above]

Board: 2 copper layers, 75.0 x 60.0 mm, 35 parts (1 on the bottom side), 27 nets.
